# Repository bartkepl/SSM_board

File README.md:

# SSM (Solidstate Switch Matrix)
Solid state relay Switch Matrix board, addon board to UCB_board 

| Top | Bottom |
|---|---|
|  |  |

---
## Status: ready for prototype order

- Schematic and PCB layout done (4-layer, 100 × 100 mm), production files generated.
- Design review completed; DRC/ERC clean (remaining items reviewed and excluded as by-design).
- Hand assembly (2 fiducials on F.Cu for stencil alignment).

Production outputs: [schematic PDF](prod/sch/SSM_board.pdf) · [PCB PDF](prod/pcb/SSM_board.pdf) · [interactive BOM](prod/ibom/SSM_board_ibom.html) · [gerbers](prod/SSM_board.zip)

---

## Features (with UCB_board):
- USB 2.0
- 10/100 Ethernet (based on WIZnet W5500)
- UART
- Half-duplex RS485 
- 3U eurocard IEEE 1101.1-1998 format (160x100 mm) — this 100 × 100 mm front module is combined with the UCB_board backend

## License and Contribution

[MIT License](/LICENSE)

Open to contributions in both software and hardware!

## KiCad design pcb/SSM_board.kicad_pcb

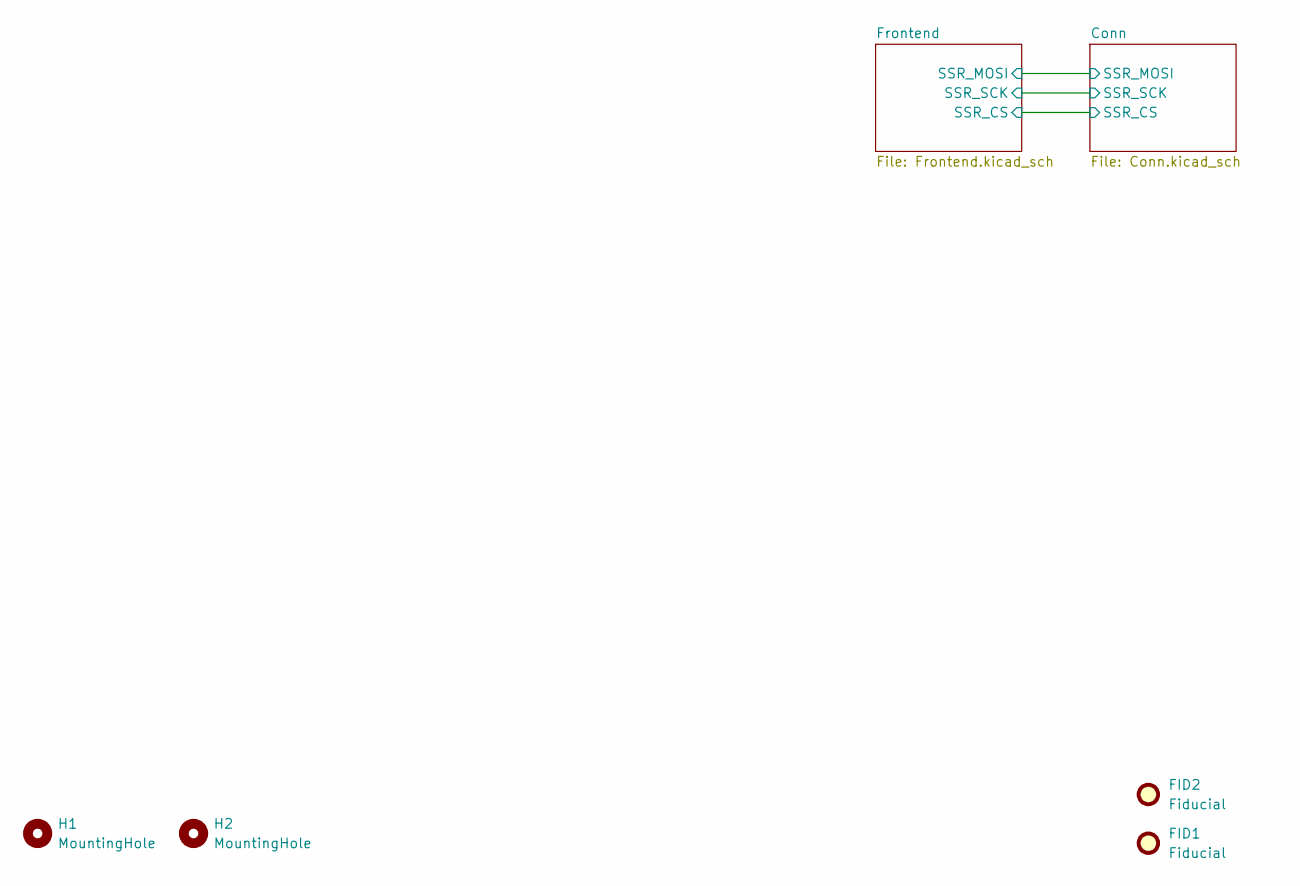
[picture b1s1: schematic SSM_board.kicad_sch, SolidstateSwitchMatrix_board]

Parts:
FID1, FID2: Fiducial; Fiducial_0.5mm_Mask1mm
H1, H2: MountingHole; MountingHole_2.7mm_M2.5

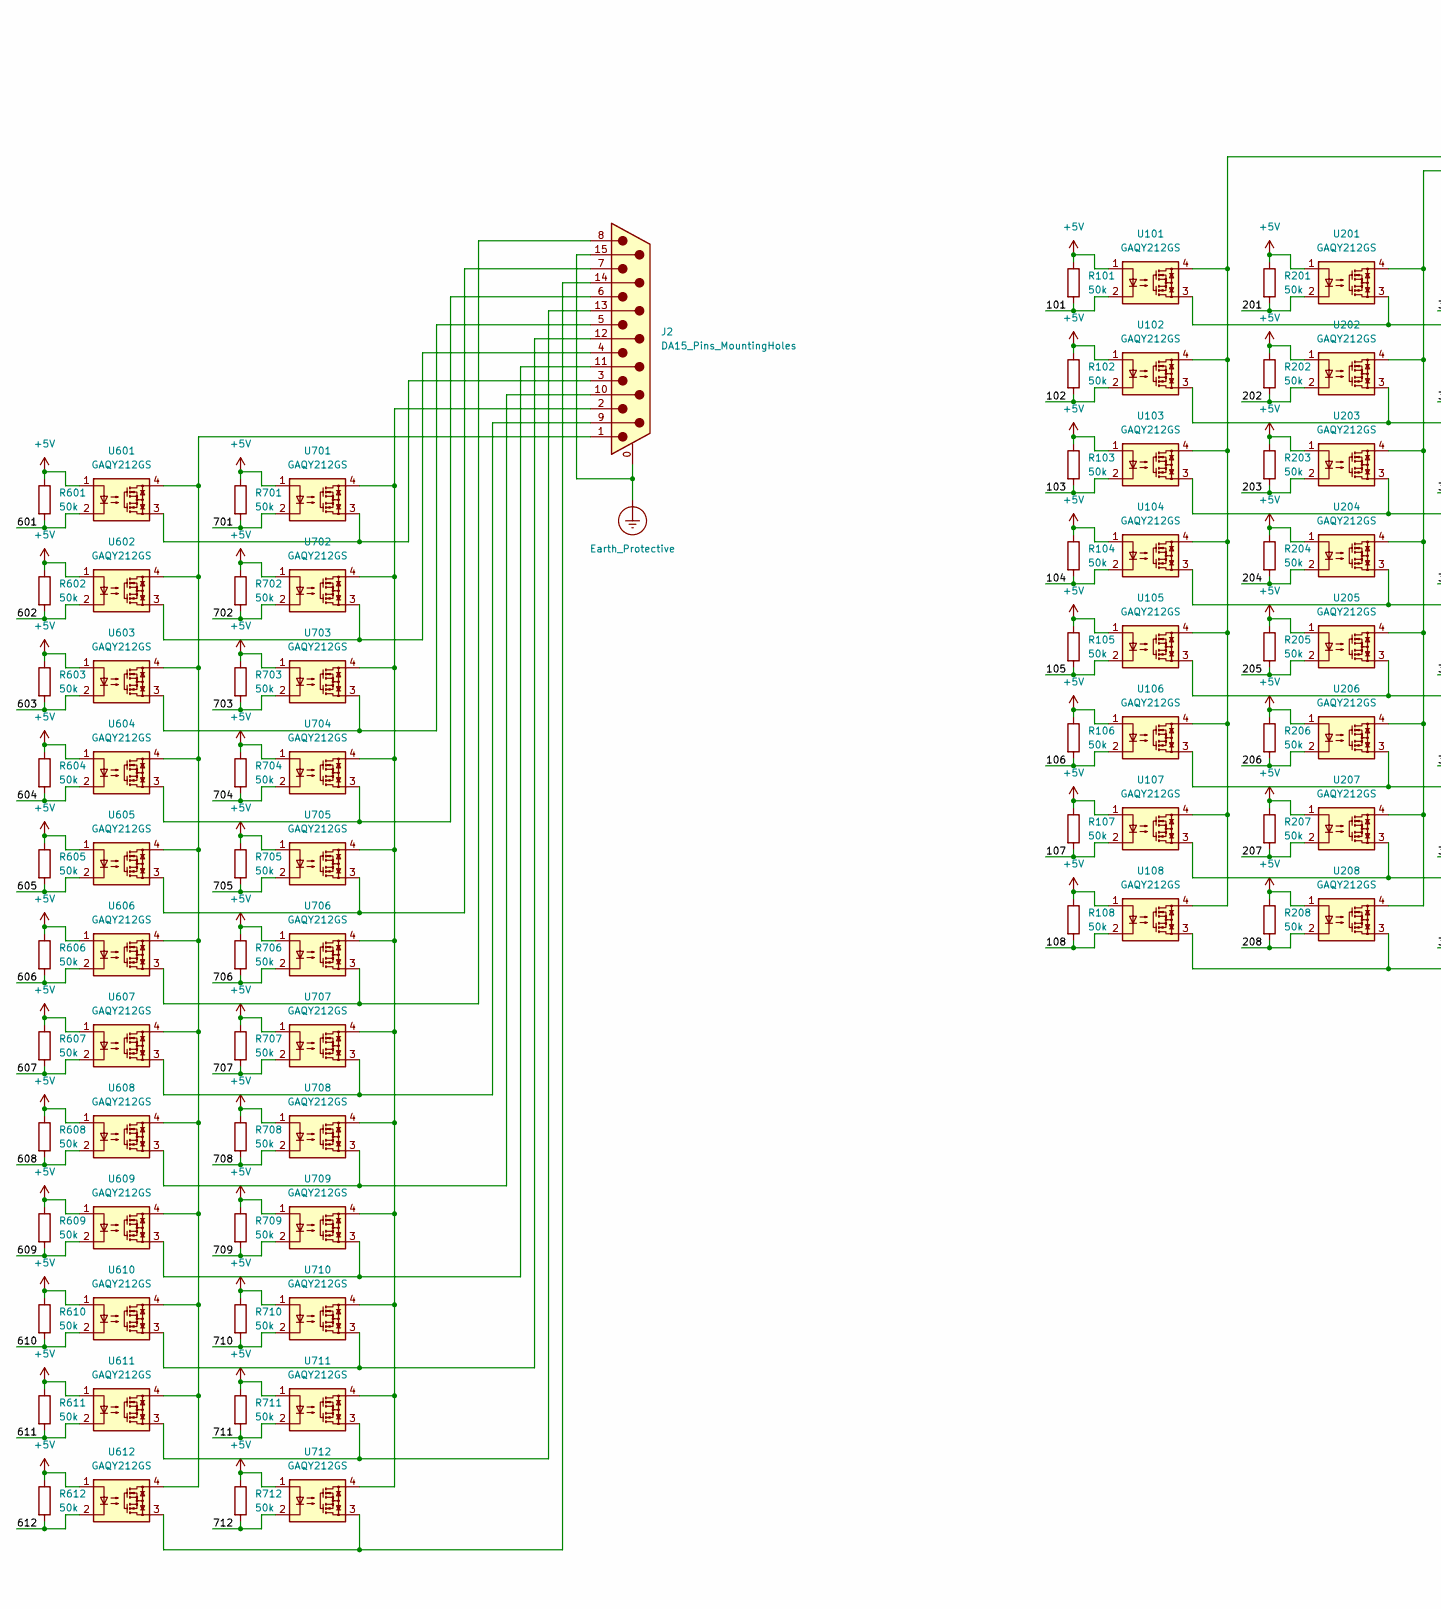
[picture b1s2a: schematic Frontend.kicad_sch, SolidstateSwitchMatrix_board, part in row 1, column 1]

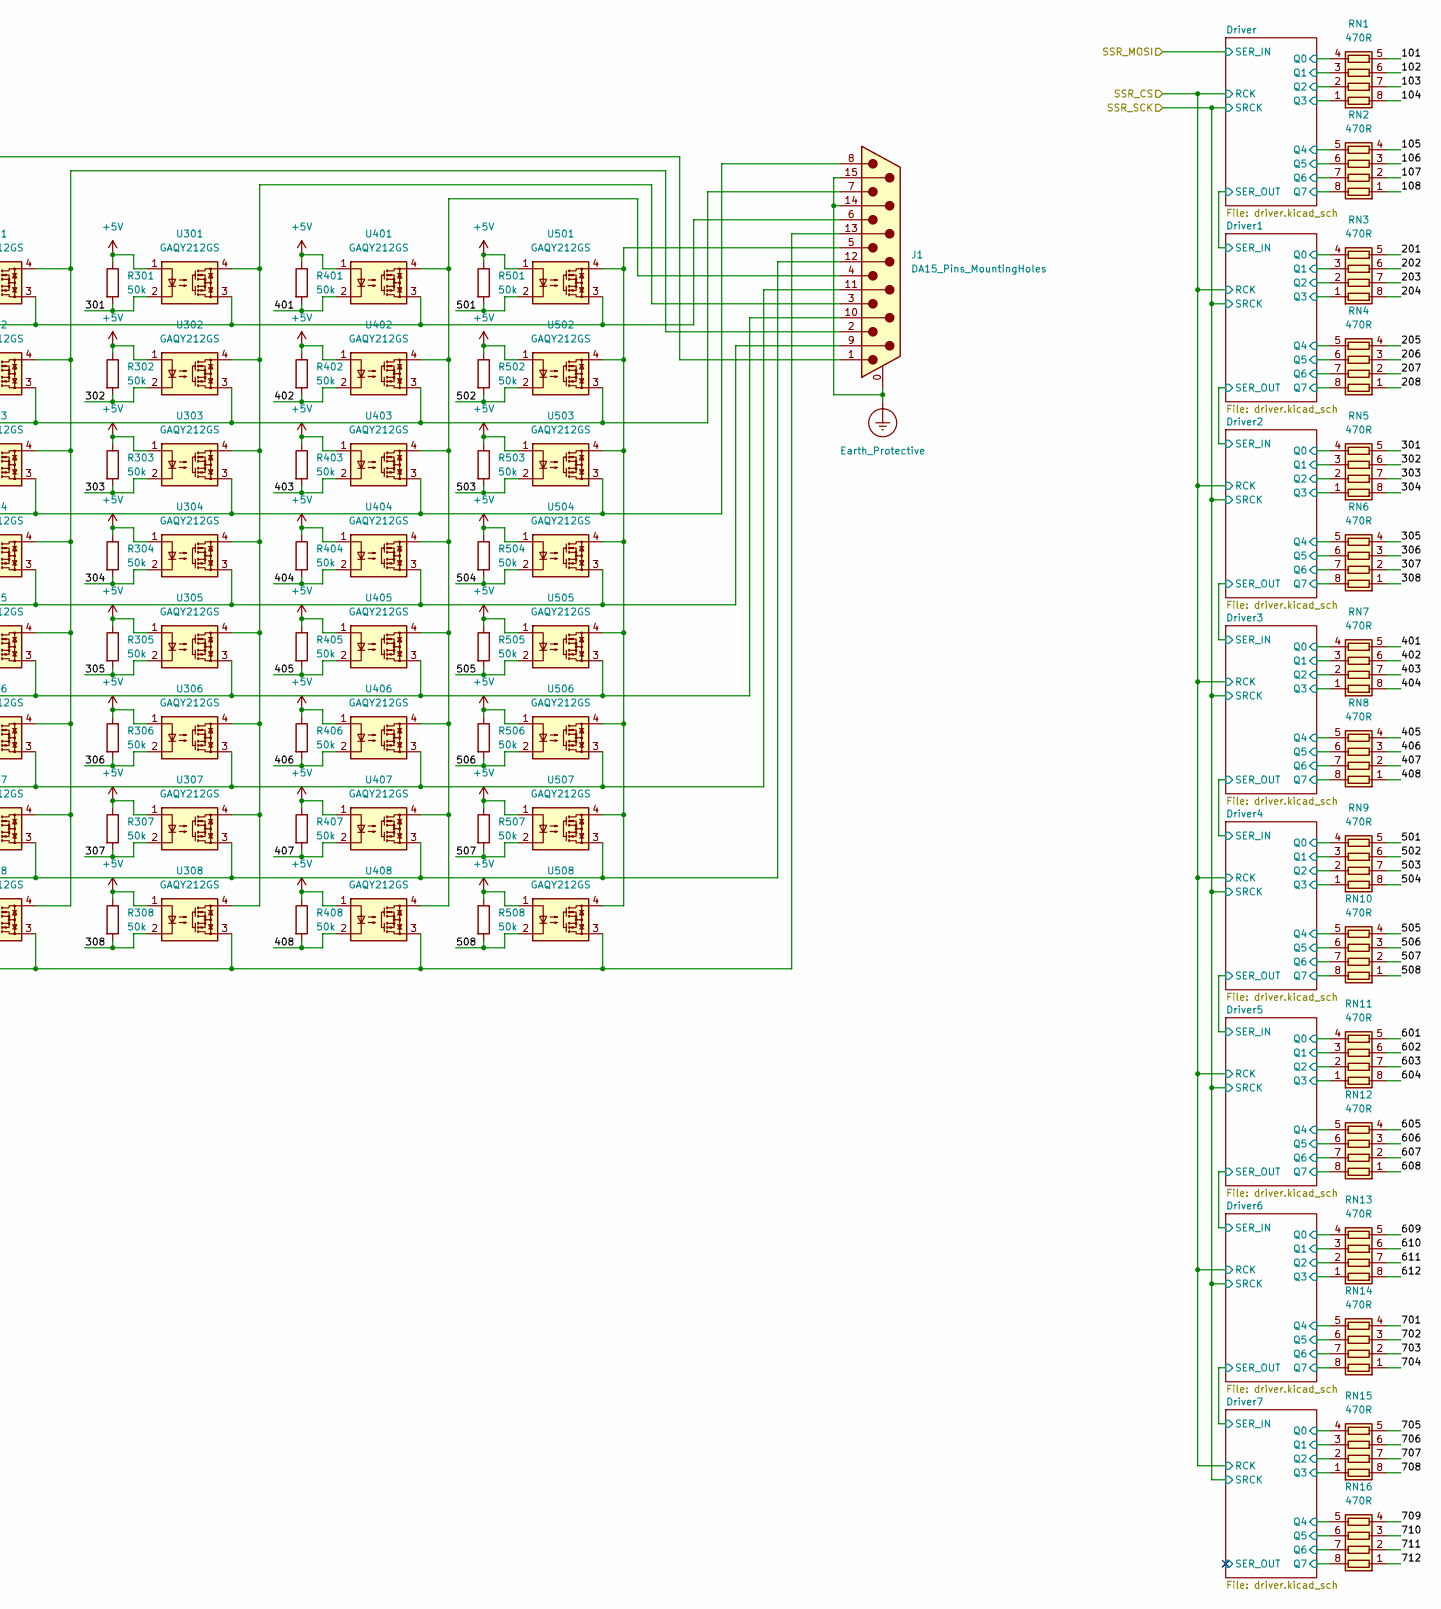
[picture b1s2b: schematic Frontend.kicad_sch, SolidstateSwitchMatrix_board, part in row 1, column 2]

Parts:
J1, J2: DA15_Pins_MountingHoles; DSUB-15_Pins_Horizontal_P2.77x2.84mm_EdgePinOffset4.94mm_Ho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
R101, R102, R103, R104, R105, R106, R107, R108, R201, R202, R203, R204, R205, R206, R207, R208, R301, R302, R303, R304, R305, R306, R307, R308, R401, R402, R403, R404, R405, R406, R407, R408, R501, R502, R503, R504, R505, R506, R507, R508, R601, R602, R603, R604, R605, R606, R607, R608, R609, R610, R611, R612, R701, R702, R703, R704, R705, R706, R707, R708, R709, R710, R711, R712: 50k; R_0603_1608Metric
RN1, RN2, RN3, RN4, RN5, RN6, RN7, RN8, RN9, RN10, RN11, RN12, RN13, RN14, RN15, RN16: 470R; R_Array_Convex_4x0603; Manufacturer_Part_Number YC164-FR-07470R
U101, U102, U103, U104, U105, U106, U107, U108, U201, U202, U203, U204, U205, U206, U207, U208, U301, U302, U303, U304, U305, U306, U307, U308, U401, U402, U403, U404, U405, U406, U407, U408, U501, U502, U503, U504, U505, U506, U507, U508, U601, U602, U603, U604, U605, U606, U607, U608, U609, U610, U611, U612, U701, U702, U703, U704, U705, U706, U707, U708, U709, U710, U711, U712: GAQY212GS; SOP-4_3.8x4.1mm_P2.54mm; Manufacturer_Part_Number GAQY212GS

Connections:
+5V: R101.1, R102.1, R103.1, R104.1, R105.1, R106.1, R107.1, R108.1, R201.1, R202.1, R203.1, R204.1, R205.1, R206.1, R207.1, R208.1, R301.1, R302.1, R303.1, R304.1, R305.1, R306.1, R307.1, R308.1, R401.1, R402.1, R403.1, R404.1, R405.1, R406.1, R407.1, R408.1, R501.1, R502.1, R503.1, R504.1, R505.1, R506.1, R507.1, R508.1, R601.1, R602.1, R603.1, R604.1, R605.1, R606.1, R607.1, R608.1, R609.1, R610.1, R611.1, R612.1, R701.1, R702.1, R703.1, R704.1, R705.1, R706.1, R707.1, R708.1, R709.1, R710.1, R711.1, R712.1, U101.1, U102.1, U103.1, U104.1, U105.1, U106.1, U107.1, U108.1, U201.1, U202.1, U203.1, U204.1, U205.1, U206.1, U207.1, U208.1, U301.1, U302.1, U303.1, U304.1, U305.1, U306.1, U307.1, U308.1, U401.1, U402.1, U403.1, U404.1, U405.1, U406.1, U407.1, U408.1, U501.1, U502.1, U503.1, U504.1, U505.1, U506.1, U507.1, U508.1, U601.1, U602.1, U603.1, U604.1, U605.1, U606.1, U607.1, U608.1, U609.1, U610.1, U611.1, U612.1, U701.1, U702.1, U703.1, U704.1, U705.1, U706.1, U707.1, U708.1, U709.1, U710.1, U711.1, U712.1; also elsewhere on the board
/Frontend/101: R101.2, RN1.5 (R4.2), U101.2
/Frontend/102: R102.2, RN1.6 (R3.2), U102.2
/Frontend/103: R103.2, RN1.7 (R2.2), U103.2
/Frontend/104: R104.2, RN1.8 (R1.2), U104.2
/Frontend/105: R105.2, RN2.4 (R4.1), U105.2
/Frontend/106: R106.2, RN2.3 (R3.1), U106.2
/Frontend/107: R107.2, RN2.2 (R2.1), U107.2
/Frontend/108: R108.2, RN2.1 (R1.1), U108.2
/Frontend/201: R201.2, RN3.5 (R4.2), U201.2
/Frontend/202: R202.2, RN3.6 (R3.2), U202.2
/Frontend/203: R203.2, RN3.7 (R2.2), U203.2
/Frontend/204: R204.2, RN3.8 (R1.2), U204.2
/Frontend/205: R205.2, RN4.4 (R4.1), U205.2
/Frontend/206: R206.2, RN4.3 (R3.1), U206.2
/Frontend/207: R207.2, RN4.2 (R2.1), U207.2
/Frontend/208: R208.2, RN4.1 (R1.1), U208.2
/Frontend/301: R301.2, RN5.5 (R4.2), U301.2
/Frontend/302: R302.2, RN5.6 (R3.2), U302.2
/Frontend/303: R303.2, RN5.7 (R2.2), U303.2
/Frontend/304: R304.2, RN5.8 (R1.2), U304.2
/Frontend/305: R305.2, RN6.4 (R4.1), U305.2
/Frontend/306: R306.2, RN6.3 (R3.1), U306.2
/Frontend/307: R307.2, RN6.2 (R2.1), U307.2
/Frontend/308: R308.2, RN6.1 (R1.1), U308.2
/Frontend/401: R401.2, RN7.5 (R4.2), U401.2
/Frontend/402: R402.2, RN7.6 (R3.2), U402.2
/Frontend/403: R403.2, RN7.7 (R2.2), U403.2
/Frontend/404: R404.2, RN7.8 (R1.2), U404.2
/Frontend/405: R405.2, RN8.4 (R4.1), U405.2
/Frontend/406: R406.2, RN8.3 (R3.1), U406.2
/Frontend/407: R407.2, RN8.2 (R2.1), U407.2
/Frontend/408: R408.2, RN8.1 (R1.1), U408.2
/Frontend/501: R501.2, RN9.5 (R4.2), U501.2
/Frontend/502: R502.2, RN9.6 (R3.2), U502.2
/Frontend/503: R503.2, RN9.7 (R2.2), U503.2
/Frontend/504: R504.2, RN9.8 (R1.2), U504.2
/Frontend/505: R505.2, RN10.4 (R4.1), U505.2
/Frontend/506: R506.2, RN10.3 (R3.1), U506.2
/Frontend/507: R507.2, RN10.2 (R2.1), U507.2
/Frontend/508: R508.2, RN10.1 (R1.1), U508.2
/Frontend/601: R601.2, RN11.5 (R4.2), U601.2
/Frontend/602: R602.2, RN11.6 (R3.2), U602.2
/Frontend/603: R603.2, RN11.7 (R2.2), U603.2
/Frontend/604: R604.2, RN11.8 (R1.2), U604.2
/Frontend/605: R605.2, RN12.4 (R4.1), U605.2
/Frontend/606: R606.2, RN12.3 (R3.1), U606.2
/Frontend/607: R607.2, RN12.2 (R2.1), U607.2
/Frontend/608: R608.2, RN12.1 (R1.1), U608.2
/Frontend/609: R609.2, RN13.5 (R4.2), U609.2
/Frontend/610: R610.2, RN13.6 (R3.2), U610.2
/Frontend/611: R611.2, RN13.7 (R2.2), U611.2
/Frontend/612: R612.2, RN13.8 (R1.2), U612.2
/Frontend/701: R701.2, RN14.4 (R4.1), U701.2
/Frontend/702: R702.2, RN14.3 (R3.1), U702.2
/Frontend/703: R703.2, RN14.2 (R2.1), U703.2
/Frontend/704: R704.2, RN14.1 (R1.1), U704.2
/Frontend/705: R705.2, RN15.5 (R4.2), U705.2
/Frontend/706: R706.2, RN15.6 (R3.2), U706.2
/Frontend/707: R707.2, RN15.7 (R2.2), U707.2
/Frontend/708: R708.2, RN15.8 (R1.2), U708.2
/Frontend/709: R709.2, RN16.4 (R4.1), U709.2
/Frontend/710: R710.2, RN16.3 (R3.1), U710.2
/Frontend/711: R711.2, RN16.2 (R2.1), U711.2
/Frontend/712: R712.2, RN16.1 (R1.1), U712.2
/Frontend/Driver1/Q0: RN3.4 (R4.1); also elsewhere on the board
/Frontend/Driver1/Q1: RN3.3 (R3.1); also elsewhere on the board
/Frontend/Driver1/Q2: RN3.2 (R2.1); also elsewhere on the board
/Frontend/Driver1/Q3: RN3.1 (R1.1); also elsewhere on the board
/Frontend/Driver1/Q4: RN4.5 (R4.2); also elsewhere on the board
/Frontend/Driver1/Q5: RN4.6 (R3.2); also elsewhere on the board
/Frontend/Driver1/Q6: RN4.7 (R2.2); also elsewhere on the board
/Frontend/Driver1/Q7: RN4.8 (R1.2); also elsewhere on the board
/Frontend/Driver2/Q0: RN5.4 (R4.1); also elsewhere on the board
/Frontend/Driver2/Q1: RN5.3 (R3.1); also elsewhere on the board
/Frontend/Driver2/Q2: RN5.2 (R2.1); also elsewhere on the board
/Frontend/Driver2/Q3: RN5.1 (R1.1); also elsewhere on the board
/Frontend/Driver2/Q4: RN6.5 (R4.2); also elsewhere on the board
/Frontend/Driver2/Q5: RN6.6 (R3.2); also elsewhere on the board
/Frontend/Driver2/Q6: RN6.7 (R2.2); also elsewhere on the board
/Frontend/Driver2/Q7: RN6.8 (R1.2); also elsewhere on the board
/Frontend/Driver3/Q0: RN7.4 (R4.1); also elsewhere on the board
/Frontend/Driver3/Q1: RN7.3 (R3.1); also elsewhere on the board
/Frontend/Driver3/Q2: RN7.2 (R2.1); also elsewhere on the board
/Frontend/Driver3/Q3: RN7.1 (R1.1); also elsewhere on the board
/Frontend/Driver3/Q4: RN8.5 (R4.2); also elsewhere on the board
/Frontend/Driver3/Q5: RN8.6 (R3.2); also elsewhere on the board
/Frontend/Driver3/Q6: RN8.7 (R2.2); also elsewhere on the board
/Frontend/Driver3/Q7: RN8.8 (R1.2); also elsewhere on the board
/Frontend/Driver4/Q0: RN9.4 (R4.1); also elsewhere on the board
/Frontend/Driver4/Q1: RN9.3 (R3.1); also elsewhere on the board
/Frontend/Driver4/Q2: RN9.2 (R2.1); also elsewhere on the board
/Frontend/Driver4/Q3: RN9.1 (R1.1); also elsewhere on the board
/Frontend/Driver4/Q4: RN10.5 (R4.2); also elsewhere on the board
/Frontend/Driver4/Q5: RN10.6 (R3.2); also elsewhere on the board
/Frontend/Driver4/Q6: RN10.7 (R2.2); also elsewhere on the board
/Frontend/Driver4/Q7: RN10.8 (R1.2); also elsewhere on the board
/Frontend/Driver5/Q0: RN11.4 (R4.1); also elsewhere on the board
/Frontend/Driver5/Q1: RN11.3 (R3.1); also elsewhere on the board
/Frontend/Driver5/Q2: RN11.2 (R2.1); also elsewhere on the board
/Frontend/Driver5/Q3: RN11.1 (R1.1); also elsewhere on the board
/Frontend/Driver5/Q4: RN12.5 (R4.2); also elsewhere on the board
/Frontend/Driver5/Q5: RN12.6 (R3.2); also elsewhere on the board
/Frontend/Driver5/Q6: RN12.7 (R2.2); also elsewhere on the board
/Frontend/Driver5/Q7: RN12.8 (R1.2); also elsewhere on the board
/Frontend/Driver6/Q0: RN13.4 (R4.1); also elsewhere on the board
/Frontend/Driver6/Q1: RN13.3 (R3.1); also elsewhere on the board
/Frontend/Driver6/Q2: RN13.2 (R2.1); also elsewhere on the board
/Frontend/Driver6/Q3: RN13.1 (R1.1); also elsewhere on the board
/Frontend/Driver6/Q4: RN14.5 (R4.2); also elsewhere on the board
/Frontend/Driver6/Q5: RN14.6 (R3.2); also elsewhere on the board
/Frontend/Driver6/Q6: RN14.7 (R2.2); also elsewhere on the board
/Frontend/Driver6/Q7: RN14.8 (R1.2); also elsewhere on the board
/Frontend/Driver7/Q0: RN15.4 (R4.1); also elsewhere on the board
/Frontend/Driver7/Q1: RN15.3 (R3.1); also elsewhere on the board
/Frontend/Driver7/Q2: RN15.2 (R2.1); also elsewhere on the board
/Frontend/Driver7/Q3: RN15.1 (R1.1); also elsewhere on the board
/Frontend/Driver7/Q4: RN16.5 (R4.2); also elsewhere on the board
/Frontend/Driver7/Q5: RN16.6 (R3.2); also elsewhere on the board
/Frontend/Driver7/Q6: RN16.7 (R2.2); also elsewhere on the board
/Frontend/Driver7/Q7: RN16.8 (R1.2); also elsewhere on the board
/Frontend/Driver/Q0: RN1.4 (R4.1); also elsewhere on the board
/Frontend/Driver/Q1: RN1.3 (R3.1); also elsewhere on the board
/Frontend/Driver/Q2: RN1.2 (R2.1); also elsewhere on the board
/Frontend/Driver/Q3: RN1.1 (R1.1); also elsewhere on the board
/Frontend/Driver/Q4: RN2.5 (R4.2); also elsewhere on the board
/Frontend/Driver/Q5: RN2.6 (R3.2); also elsewhere on the board
/Frontend/Driver/Q6: RN2.7 (R2.2); also elsewhere on the board
/Frontend/Driver/Q7: RN2.8 (R1.2); also elsewhere on the board
Earth_Protective: J1.0 (PAD), J1.14, J1.15, J2.0 (PAD), J2.15; also elsewhere on the board
unnamed: J1.9, U104.3, U204.3, U304.3, U404.3, U504.3
unnamed: J1.10, U105.3, U205.3, U305.3, U405.3, U505.3
unnamed: J1.12, U107.3, U207.3, U307.3, U407.3, U507.3
unnamed: J1.13, U108.3, U208.3, U308.3, U408.3, U508.3
unnamed: J1.11 (P111), U106.3, U206.3, U306.3, U406.3, U506.3
unnamed: J1.1, U101.4, U102.4, U103.4, U104.4, U105.4, U106.4, U107.4, U108.4
unnamed: J1.2, U201.4, U202.4, U203.4, U204.4, U205.4, U206.4, U207.4, U208.4
unnamed: J1.3, U301.4, U302.4, U303.4, U304.4, U305.4, U306.4, U307.4, U308.4
unnamed: J1.4, U401.4, U402.4, U403.4, U404.4, U405.4, U406.4, U407.4, U408.4
unnamed: J1.5, U501.4, U502.4, U503.4, U504.4, U505.4, U506.4, U507.4, U508.4
unnamed: J1.6, U101.3, U201.3, U301.3, U401.3, U501.3
unnamed: J1.7, U102.3, U202.3, U302.3, U402.3, U502.3
unnamed: J1.8, U103.3, U203.3, U303.3, U403.3, U503.3
unnamed: J2.9, U607.3, U707.3
unnamed: J2.10, U608.3, U708.3
unnamed: J2.12, U610.3, U710.3
unnamed: J2.13, U611.3, U711.3
unnamed: J2.14, U612.3, U712.3
unnamed: J2.11 (P111), U609.3, U709.3
unnamed: J2.1, U601.4, U602.4, U603.4, U604.4, U605.4, U606.4, U607.4, U608.4, U609.4, U610.4, U611.4, U612.4
unnamed: J2.2, U701.4, U702.4, U703.4, U704.4, U705.4, U706.4, U707.4, U708.4, U709.4, U710.4, U711.4, U712.4
unnamed: J2.3, U601.3, U701.3
unnamed: J2.4, U602.3, U702.3
unnamed: J2.5, U603.3, U703.3
unnamed: J2.6, U604.3, U704.3
unnamed: J2.7, U605.3, U705.3
unnamed: J2.8, U606.3, U706.3

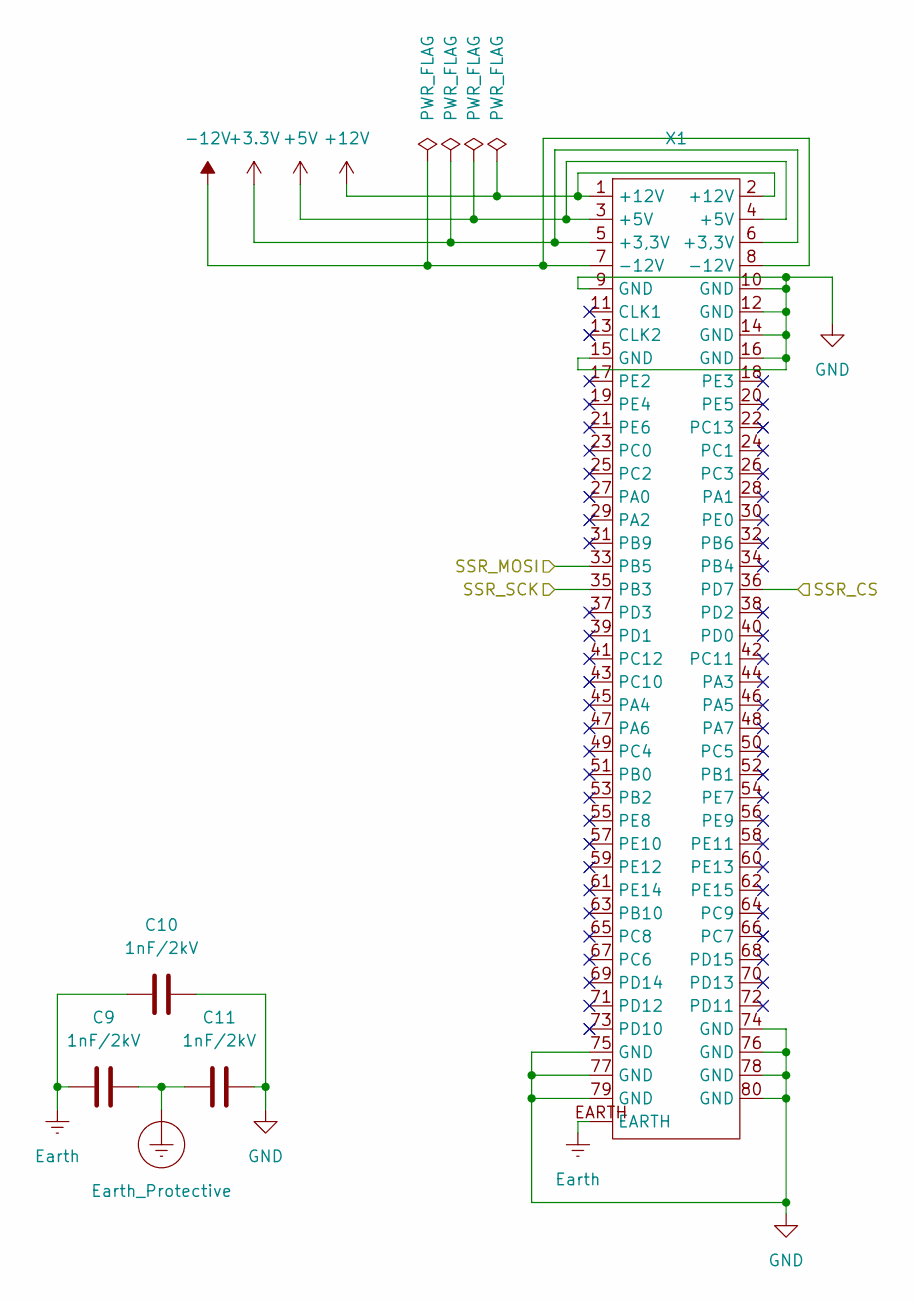
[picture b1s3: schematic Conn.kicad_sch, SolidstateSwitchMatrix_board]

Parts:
C9, C10, C11: 1nF/2kV; C_1206_3216Metric; Manufacturer_Part_Number 1206B102K202
X1: UCB_conn

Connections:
+3.3V: X1.5 (+3,3V), X1.6 (+3,3V)
+5V: X1.3 (+5V), X1.4 (+5V); also elsewhere on the board
+12V: X1.1 (+12V), X1.2 (+12V)
-12V: X1.7 (-12V), X1.8 (-12V)
/Conn/SSR_CS: X1.36 (PD7); also elsewhere on the board
/Conn/SSR_MOSI: X1.33 (PB5); also elsewhere on the board
/Conn/SSR_SCK: X1.35 (PB3); also elsewhere on the board
Earth: C9.1, C10.1, X1.EARTH
Earth_Protective: C9.2, C11.1; also elsewhere on the board
GND: C10.2, C11.2, X1.9 (GND), X1.10 (GND), X1.12 (GND), X1.14 (GND), X1.15 (GND), X1.16 (GND), X1.74 (GND), X1.75 (GND), X1.76 (GND), X1.77 (GND), X1.78 (GND), X1.79 (GND), X1.80 (GND); also elsewhere on the board

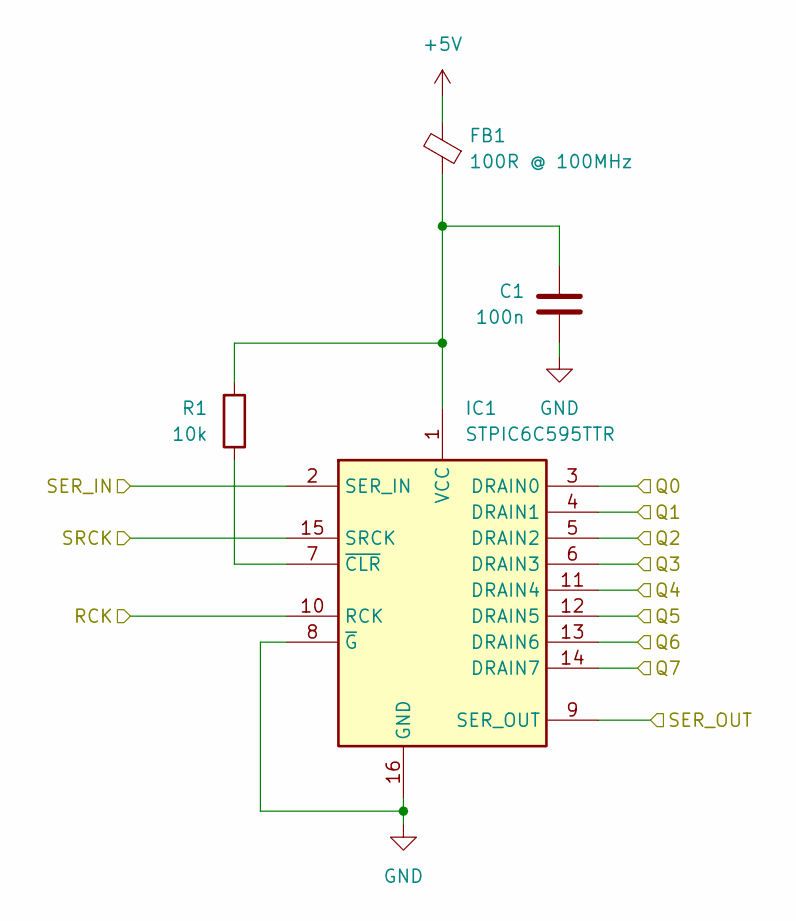
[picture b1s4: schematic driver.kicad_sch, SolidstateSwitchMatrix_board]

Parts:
C1: 100n; C_0603_1608Metric
FB1: 100R @ 100MHz; L_0603_1608Metric; Manufacturer_Part_Number WLBD1608HCU101TL
IC1: STPIC6C595TTR; SOP65P640X120-16N; Manufacturer_Part_Number STPIC6C595TTR
R1: 10k; R_0603_1608Metric; Manufacturer_Part_Number CRCW060310K0FKTABC

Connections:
+5V: FB1.2; also elsewhere on the board
/Conn/SSR_CS: IC1.10 (RCK); also elsewhere on the board
/Conn/SSR_MOSI: IC1.2 (SER_IN); also elsewhere on the board
/Conn/SSR_SCK: IC1.15 (SRCK); also elsewhere on the board
/Frontend/Driver/Q0: IC1.3 (DRAIN0); also elsewhere on the board
/Frontend/Driver/Q1: IC1.4 (DRAIN1); also elsewhere on the board
/Frontend/Driver/Q2: IC1.5 (DRAIN2); also elsewhere on the board
/Frontend/Driver/Q3: IC1.6 (DRAIN3); also elsewhere on the board
/Frontend/Driver/Q4: IC1.11 (DRAIN4); also elsewhere on the board
/Frontend/Driver/Q5: IC1.12 (DRAIN5); also elsewhere on the board
/Frontend/Driver/Q6: IC1.13 (DRAIN6); also elsewhere on the board
/Frontend/Driver/Q7: IC1.14 (DRAIN7); also elsewhere on the board
/Frontend/Driver/SER_OUT: IC1.9 (SER_OUT); also elsewhere on the board
GND: C1.1, IC1.8 (~G), IC1.16 (GND); also elsewhere on the board
unnamed: C1.2, FB1.1, IC1.1 (VCC), R1.2
unnamed: IC1.7 (~CLR), R1.1

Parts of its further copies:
C2, C3, C4, C5, C6, C7, C8: 100n; C_0603_1608Metric
FB2, FB3, FB4, FB5, FB6, FB7, FB8: 100R @ 100MHz; L_0603_1608Metric; Manufacturer_Part_Number WLBD1608HCU101TL
IC2, IC3, IC4, IC5, IC6, IC7, IC8: STPIC6C595TTR; SOP65P640X120-16N; Manufacturer_Part_Number STPIC6C595TTR
R2, R3, R4, R5, R6, R7, R8: 10k; R_0603_1608Metric; Manufacturer_Part_Number CRCW060310K0FKTABC

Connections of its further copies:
+5V: FB2.2, FB3.2, FB4.2, FB5.2, FB6.2, FB7.2, FB8.2; also elsewhere on the board
/Conn/SSR_CS: IC2.10 (RCK), IC3.10 (RCK), IC4.10 (RCK), IC5.10 (RCK), IC6.10 (RCK), IC7.10 (RCK), IC8.10 (RCK); also elsewhere on the board
/Conn/SSR_SCK: IC2.15 (SRCK), IC3.15 (SRCK), IC4.15 (SRCK), IC5.15 (SRCK), IC6.15 (SRCK), IC7.15 (SRCK), IC8.15 (SRCK); also elsewhere on the board
/Frontend/Driver1/Q0: IC2.3 (DRAIN0); also elsewhere on the board
/Frontend/Driver1/Q1: IC2.4 (DRAIN1); also elsewhere on the board
/Frontend/Driver1/Q2: IC2.5 (DRAIN2); also elsewhere on the board
/Frontend/Driver1/Q3: IC2.6 (DRAIN3); also elsewhere on the board
/Frontend/Driver1/Q4: IC2.11 (DRAIN4); also elsewhere on the board
/Frontend/Driver1/Q5: IC2.12 (DRAIN5); also elsewhere on the board
/Frontend/Driver1/Q6: IC2.13 (DRAIN6); also elsewhere on the board
/Frontend/Driver1/Q7: IC2.14 (DRAIN7); also elsewhere on the board
/Frontend/Driver1/SER_OUT: IC2.9 (SER_OUT), IC3.2 (SER_IN)
/Frontend/Driver2/Q0: IC3.3 (DRAIN0); also elsewhere on the board
/Frontend/Driver2/Q1: IC3.4 (DRAIN1); also elsewhere on the board
/Frontend/Driver2/Q2: IC3.5 (DRAIN2); also elsewhere on the board
/Frontend/Driver2/Q3: IC3.6 (DRAIN3); also elsewhere on the board
/Frontend/Driver2/Q4: IC3.11 (DRAIN4); also elsewhere on the board
/Frontend/Driver2/Q5: IC3.12 (DRAIN5); also elsewhere on the board
/Frontend/Driver2/Q6: IC3.13 (DRAIN6); also elsewhere on the board
/Frontend/Driver2/Q7: IC3.14 (DRAIN7); also elsewhere on the board
/Frontend/Driver2/SER_OUT: IC3.9 (SER_OUT), IC4.2 (SER_IN)
/Frontend/Driver3/Q0: IC4.3 (DRAIN0); also elsewhere on the board
/Frontend/Driver3/Q1: IC4.4 (DRAIN1); also elsewhere on the board
/Frontend/Driver3/Q2: IC4.5 (DRAIN2); also elsewhere on the board
/Frontend/Driver3/Q3: IC4.6 (DRAIN3); also elsewhere on the board
/Frontend/Driver3/Q4: IC4.11 (DRAIN4); also elsewhere on the board
/Frontend/Driver3/Q5: IC4.12 (DRAIN5); also elsewhere on the board
/Frontend/Driver3/Q6: IC4.13 (DRAIN6); also elsewhere on the board
/Frontend/Driver3/Q7: IC4.14 (DRAIN7); also elsewhere on the board
/Frontend/Driver3/SER_OUT: IC4.9 (SER_OUT), IC5.2 (SER_IN)
/Frontend/Driver4/Q0: IC5.3 (DRAIN0); also elsewhere on the board
/Frontend/Driver4/Q1: IC5.4 (DRAIN1); also elsewhere on the board
/Frontend/Driver4/Q2: IC5.5 (DRAIN2); also elsewhere on the board
/Frontend/Driver4/Q3: IC5.6 (DRAIN3); also elsewhere on the board
/Frontend/Driver4/Q4: IC5.11 (DRAIN4); also elsewhere on the board
/Frontend/Driver4/Q5: IC5.12 (DRAIN5); also elsewhere on the board
/Frontend/Driver4/Q6: IC5.13 (DRAIN6); also elsewhere on the board
/Frontend/Driver4/Q7: IC5.14 (DRAIN7); also elsewhere on the board
/Frontend/Driver4/SER_OUT: IC5.9 (SER_OUT), IC6.2 (SER_IN)
/Frontend/Driver5/Q0: IC6.3 (DRAIN0); also elsewhere on the board
/Frontend/Driver5/Q1: IC6.4 (DRAIN1); also elsewhere on the board
/Frontend/Driver5/Q2: IC6.5 (DRAIN2); also elsewhere on the board
/Frontend/Driver5/Q3: IC6.6 (DRAIN3); also elsewhere on the board
/Frontend/Driver5/Q4: IC6.11 (DRAIN4); also elsewhere on the board
/Frontend/Driver5/Q5: IC6.12 (DRAIN5); also elsewhere on the board
/Frontend/Driver5/Q6: IC6.13 (DRAIN6); also elsewhere on the board
/Frontend/Driver5/Q7: IC6.14 (DRAIN7); also elsewhere on the board
/Frontend/Driver5/SER_OUT: IC6.9 (SER_OUT), IC7.2 (SER_IN)
/Frontend/Driver6/Q0: IC7.3 (DRAIN0); also elsewhere on the board
/Frontend/Driver6/Q1: IC7.4 (DRAIN1); also elsewhere on the board
/Frontend/Driver6/Q2: IC7.5 (DRAIN2); also elsewhere on the board
/Frontend/Driver6/Q3: IC7.6 (DRAIN3); also elsewhere on the board
/Frontend/Driver6/Q4: IC7.11 (DRAIN4); also elsewhere on the board
/Frontend/Driver6/Q5: IC7.12 (DRAIN5); also elsewhere on the board
/Frontend/Driver6/Q6: IC7.13 (DRAIN6); also elsewhere on the board
/Frontend/Driver6/Q7: IC7.14 (DRAIN7); also elsewhere on the board
/Frontend/Driver6/SER_OUT: IC7.9 (SER_OUT), IC8.2 (SER_IN)
/Frontend/Driver7/Q0: IC8.3 (DRAIN0); also elsewhere on the board
/Frontend/Driver7/Q1: IC8.4 (DRAIN1); also elsewhere on the board
/Frontend/Driver7/Q2: IC8.5 (DRAIN2); also elsewhere on the board
/Frontend/Driver7/Q3: IC8.6 (DRAIN3); also elsewhere on the board
/Frontend/Driver7/Q4: IC8.11 (DRAIN4); also elsewhere on the board
/Frontend/Driver7/Q5: IC8.12 (DRAIN5); also elsewhere on the board
/Frontend/Driver7/Q6: IC8.13 (DRAIN6); also elsewhere on the board
/Frontend/Driver7/Q7: IC8.14 (DRAIN7); also elsewhere on the board
/Frontend/Driver7/SER_OUT: IC8.9 (SER_OUT)
/Frontend/Driver/SER_OUT: IC2.2 (SER_IN); also elsewhere on the board
GND: C2.1, C3.1, C4.1, C5.1, C6.1, C7.1, C8.1, IC2.8 (~G), IC2.16 (GND), IC3.8 (~G), IC3.16 (GND), IC4.8 (~G), IC4.16 (GND), IC5.8 (~G), IC5.16 (GND), IC6.8 (~G), IC6.16 (GND), IC7.8 (~G), IC7.16 (GND), IC8.8 (~G), IC8.16 (GND); also elsewhere on the board
unnamed: C2.2, FB2.1, IC2.1 (VCC), R2.2
unnamed: IC2.7 (~CLR), R2.1
unnamed: C3.2, FB3.1, IC3.1 (VCC), R3.2
unnamed: IC3.7 (~CLR), R3.1
unnamed: C4.2, FB4.1, IC4.1 (VCC), R4.2
unnamed: IC4.7 (~CLR), R4.1
unnamed: C5.2, FB5.1, IC5.1 (VCC), R5.2
unnamed: IC5.7 (~CLR), R5.1
unnamed: C6.2, FB6.1, IC6.1 (VCC), R6.2
unnamed: IC6.7 (~CLR), R6.1
unnamed: C7.2, FB7.1, IC7.1 (VCC), R7.2
unnamed: IC7.7 (~CLR), R7.1
unnamed: C8.2, FB8.1, IC8.1 (VCC), R8.2
unnamed: IC8.7 (~CLR), R8.1

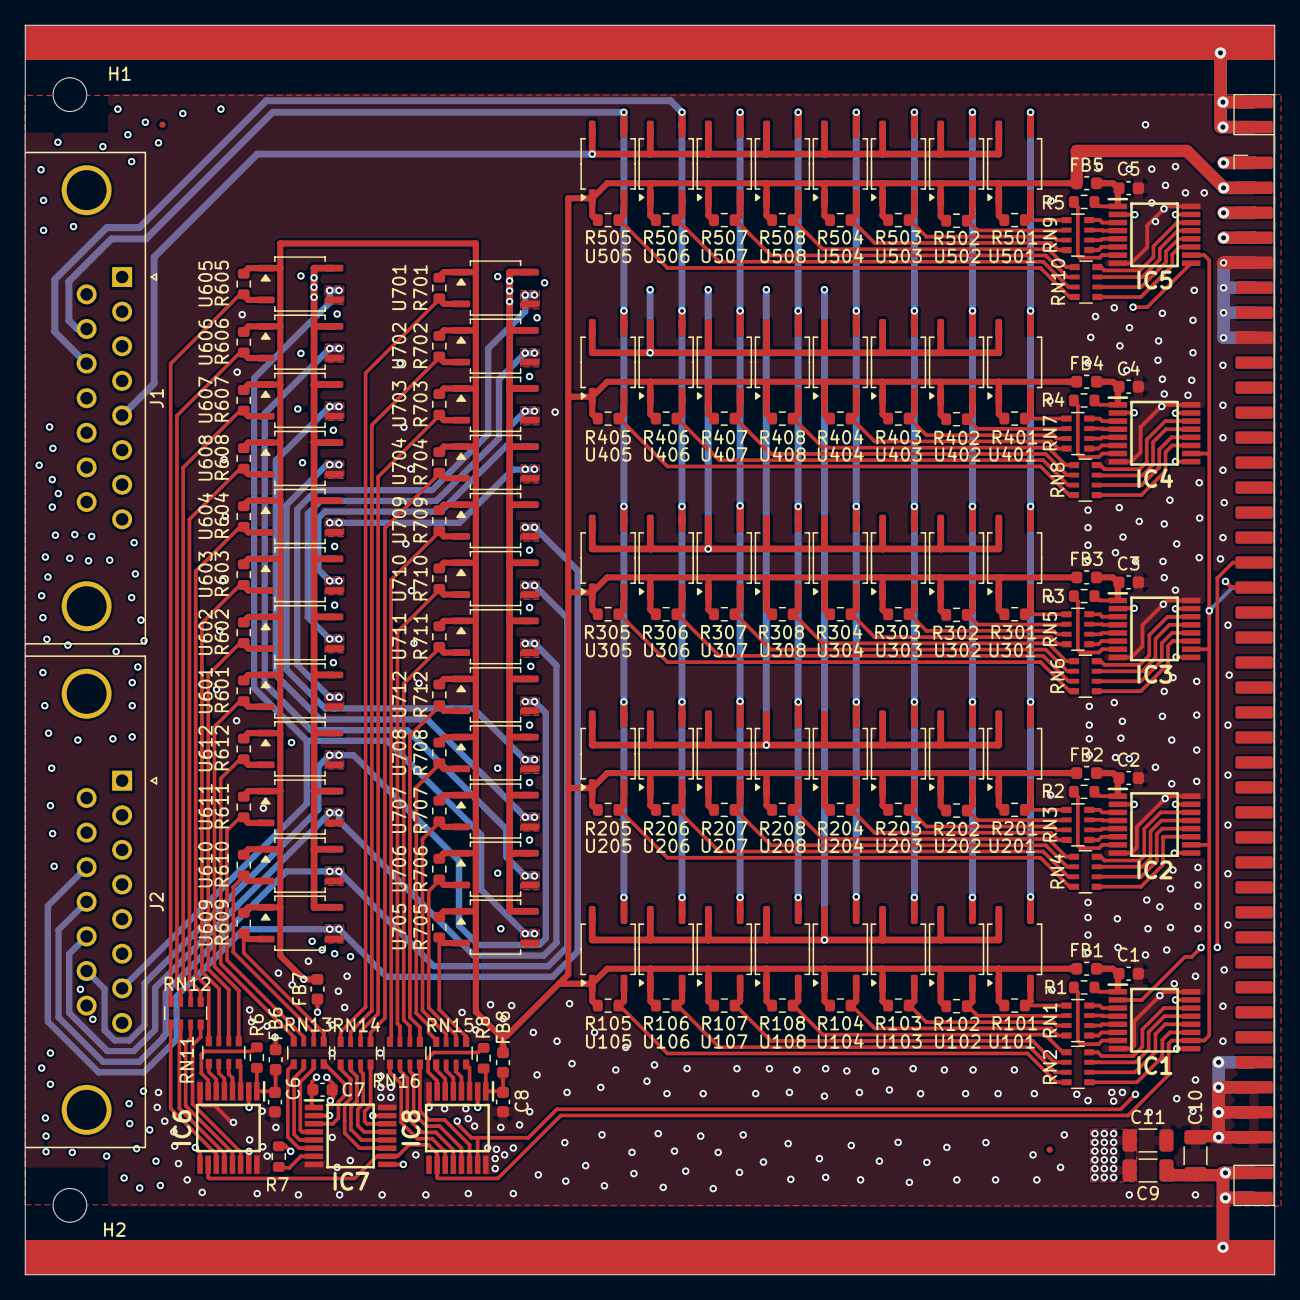
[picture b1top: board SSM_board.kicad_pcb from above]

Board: 4 copper layers, 100.0 x 100.0 mm, 186 parts (0 on the bottom side), 188 nets.

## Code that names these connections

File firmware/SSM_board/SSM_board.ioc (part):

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Mcu.Name=STM32H563VITx
Mcu.Package=LQFP100
Mcu.UserName=STM32H563VITx
PA10.Mode=Asynchronous
PA10.Signal=USART1_RX
PA11.Mode=Device
PA11.Signal=USB_DM
PA12.Mode=Device
PA12.Signal=USB_DP
PA13(JTMS/SWDIO).Mode=Serial_Wire
PA13(JTMS/SWDIO).Signal=DEBUG_JTMS-SWDIO
PA14(JTCK/SWCLK).Mode=Serial_Wire
PA14(JTCK/SWCLK).Signal=DEBUG_JTCK-SWCLK
PA15(JTDI).GPIOParameters=GPIO_Label
PA15(JTDI).GPIO_Label=USB_DETECT
PA15(JTDI).Signal=GPIO_Input
PA8.Mode=Clock-out
PA8.Signal=RCC_MCO_1
PA9.Mode=Asynchronous
PA9.Signal=USART1_TX
PB12.GPIOParameters=GPIO_Label
PB12.GPIO_Label=W5500_CS
PB12.Signal=GPIO_Output
PB13.GPIOParameters=GPIO_Label
PB13.GPIO_Label=W5500_SCK
PB13.Mode=Full_Duplex_Master
PB13.Signal=SPI2_SCK
PB14.GPIOParameters=GPIO_Label
PB14.GPIO_Label=W5500_MISO
PB14.Mode=Full_Duplex_Master
PB14.Signal=SPI2_MISO
PB15.GPIOParameters=GPIO_Label
PB15.GPIO_Label=W5500_MOSI
PB15.Mode=Full_Duplex_Master
PB15.Signal=SPI2_MOSI
PB3(JTDO/TRACESWO).GPIOParameters=GPIO_Label
PB3(JTDO/TRACESWO).GPIO_Label=SSR_SCK
PB3(JTDO/TRACESWO).Mode=TX_Only_Simplex_Unidirect_Master
PB3(JTDO/TRACESWO).Signal=SPI1_SCK
PB5.GPIOParameters=GPIO_Label
PB5.GPIO_Label=SSR_MOSI
PB5.Mode=TX_Only_Simplex_Unidirect_Master
PB5.Signal=SPI1_MOSI
PB7.Mode=I2C
PB7.Signal=I2C1_SDA
PB8.Mode=I2C
PB8.Signal=I2C1_SCL
PC14-OSC32_IN(OSC32_IN).Signal=GPIO_Output
PC15-OSC32_OUT(OSC32_OUT).Signal=GPIO_Output
PD4.Mode=Hardware Flow Control (RS485)
PD4.Signal=USART2_DE
PD5.Mode=Asynchronous
PD5.Signal=USART2_TX
PD6.Mode=Asynchronous
PD6.Signal=USART2_RX
PD7.GPIOParameters=GPIO_Label
PD7.GPIO_Label=SSR_CS
PD7.Signal=GPIO_Output
PD8.GPIOParameters=GPIO_Label
PD8.GPIO_Label=W5500_RST
PD8.Signal=GPIO_Output
PD9.GPIOParameters=GPIO_Label
PD9.GPIO_Label=W5500_INT
PD9.Signal=GPIO_Input
PH0-OSC_IN(PH0).Mode=HSE-External-Oscillator
PH0-OSC_IN(PH0).Signal=RCC_OSC_IN
PH1-OSC_OUT(PH1).Mode=HSE-External-Oscillator
PH1-OSC_OUT(PH1).Signal=RCC_OSC_OUT
RCC.HSE_VALUE=25000000
RCC.SYSCLKFreq_VALUE=200000000
RCC.SYSCLKSource=RCC_SYSCLKSOURCE_PLLCLK
board=custom

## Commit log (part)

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2026-05-14 Functional block routing
2026-05-15 More routing
2026-05-15 Routing done, left via stitching and silkscreen collisions
2026-05-17 Add earth symbols, capacitors and teardrops
    Add protective earth/earth power symbols and instances to the Conn schematic, plus wiring/junctions to connect them. Add three SMD capacitors (C9, C10, C11) to the schematic and link them to a 1206 h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
2026-05-18 Added vias
